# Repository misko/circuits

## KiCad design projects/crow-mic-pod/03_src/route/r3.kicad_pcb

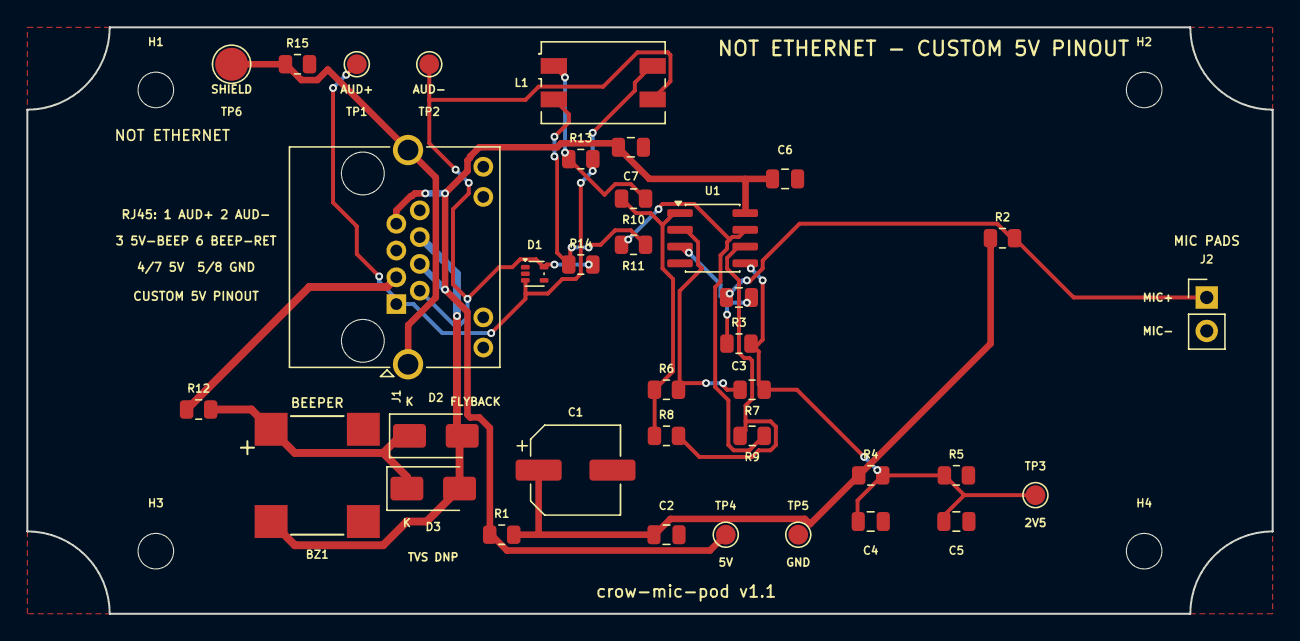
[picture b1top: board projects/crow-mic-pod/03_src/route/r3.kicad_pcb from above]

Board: 2 copper layers, 94.5 x 44.5 mm, 40 parts (0 on the bottom side), 18 nets.

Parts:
BZ1: CMT-8504-100-SMT-TR; CMT-8504
C1: 100u 5VF; CP_Elec_6.3x5.4
C2: 100n 5VF; C_0805_2012Metric
C3: 1u coupling; C_0805_2012Metric
C4: 10u VMID; C_0805_2012Metric
C5: 100n VMID; C_0805_2012Metric
C6: 100n U1; C_0805_2012Metric
C7: 10u 5V bulk; C_0805_2012Metric
D1: TPD2E2U06DRLR; SOT-553
D2: SS14 flyback; D_SMA
D3: SMAJ6.0A TVS DNP; D_SMA
H1, H2, H3, H4: MountingHole_2.7mm_M2.5
J1: RJHSE-5384; RJ45_Amphenol_RJHSE538X
J2: MIC PADS (AOM-5024L); PinHeader_1x02_P2.54mm_Vertical
L1: CM choke DNP; L_CommonMode_Wuerth_WE-SL2
R1: 100R 5VF; R_0805_2012Metric
R2: 3.9k mic bias; R_0805_2012Metric
R3: 100k bias; R_0805_2012Metric
R4: 10k div hi; R_0805_2012Metric
R5: 10k div lo; R_0805_2012Metric
R6: 10k fb A; R_0805_2012Metric
R7: 20k gain A; R_0805_2012Metric
R8: 20k inv in; R_0805_2012Metric
R9: 20k inv fb; R_0805_2012Metric
R10: 68R iso +; R_0805_2012Metric
R11: 68R iso -; R_0805_2012Metric
R12: 0R beep series; R_0805_2012Metric
R13: 0R choke byp +; R_0805_2012Metric
R14: 0R choke byp -; R_0805_2012Metric
R15: shield bond DNP; R_0805_2012Metric
TP1: TP AUDIO+; TestPoint_Pad_D1.5mm
TP2: TP AUDIO-; TestPoint_Pad_D1.5mm
TP3: TP 2V5 MID; TestPoint_Pad_D1.5mm
TP4: TP 5V; TestPoint_Pad_D1.5mm
TP5: TP GND; TestPoint_Pad_D1.5mm
TP6: SHIELD BOND PAD; TestPoint_Pad_D2.5mm
U1: OPA1678IDR; SOIC-8_3.9x4.9mm_P1.27mm

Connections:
5V: C6.1, C7.1, J1.4, J1.7, R1.1, TP4.1, U1.8
5VF: C1.1, C2.1, R1.2, R2.1, R4.1
AIN: C3.2, R3.1, U1.3
AUDIO_N: D1.5, J1.2, L1.3, R14.2, TP2.1
AUDIO_P: D1.3, J1.1, L1.4, R13.2, TP1.1
AUD_N_I: L1.2, R11.2, R14.1
AUD_P_I: L1.1, R10.2, R13.1
A_OUT: R6.1, R8.1, R10.1, U1.1
BEEP_5V: J1.3, R12.1
BEEP_RET: BZ1.2, D2.2, D3.2, J1.6
BZ_P: BZ1.1, D2.1, D3.1, R12.2
B_OUT: R9.2, R11.1, U1.7
FB_A: R6.2, R7.1, U1.2
FB_B: R8.2, R9.1, U1.6
GND: C1.2, C2.2, C4.2, C5.2, C6.2, C7.2, D1.4, J1.5, J1.8, J2.2, R5.2, R15.2, TP5.1, U1.4
MIC: C3.1, J2.1, R2.2
SHIELD: J1.SH, R15.1, TP6.1
VMID: C4.1, C5.1, R3.2, R4.2, R5.1, R7.2, TP3.1, U1.5

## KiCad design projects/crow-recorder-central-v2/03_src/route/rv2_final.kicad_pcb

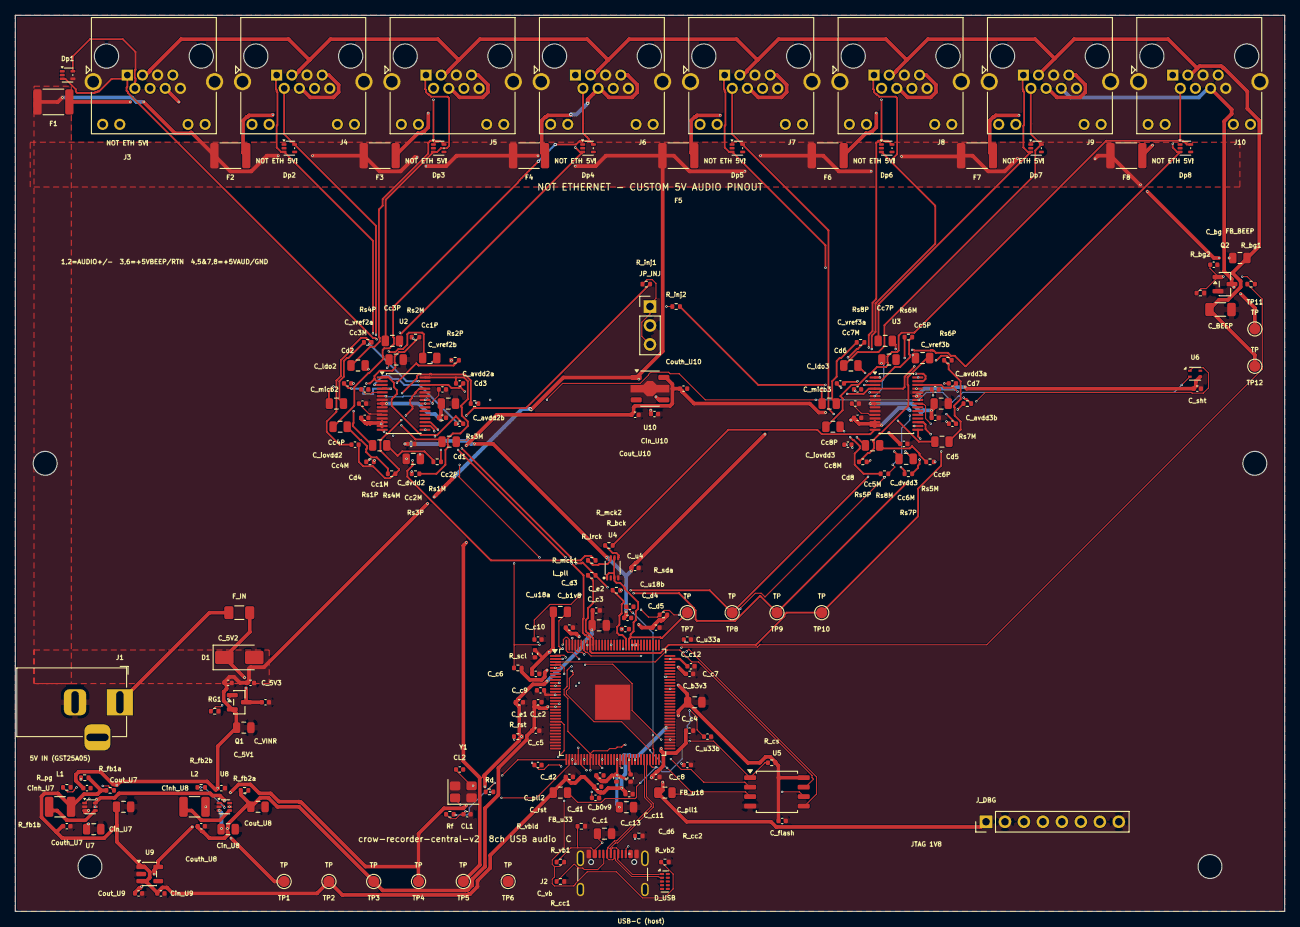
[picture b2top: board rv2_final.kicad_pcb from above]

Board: 6 copper layers, 170.0 x 120.0 mm, 203 parts (0 on the bottom side), 116 nets.

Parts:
CL1, CL2: 12pF; C_0402_1005Metric
C_5V1: 22uF; C_0805_2012Metric
C_5V2, C_5V3: 100nF; C_0402_1005Metric
C_BEEP: 47uF; C_1206_3216Metric
C_VINR: 100nF; C_0402_1005Metric
C_avdd2a, C_avdd3a: 10uF; C_0805_2012Metric
C_avdd2b, C_avdd3b: 100nF; C_0402_1005Metric
C_b0v9, C_b1v8, C_b3v3: 10uF; C_0805_2012Metric
C_bg: 4.7nF; C_0402_1005Metric
C_c1, C_c2, C_c3, C_c4, C_c5, C_c6, C_c7, C_c8, C_c9, C_c10, C_c11, C_c12, C_c13: 100nF; C_0402_1005Metric
C_d1, C_d2, C_d3, C_d4, C_d5, C_d6: 100nF; C_0402_1005Metric
C_dvdd2, C_dvdd3: 100nF; C_0402_1005Metric
C_e1, C_e2: 100nF; C_0402_1005Metric
C_flash: 100nF; C_0402_1005Metric
C_iovdd2, C_iovdd3: 100nF; C_0402_1005Metric
C_ldo2, C_ldo3: 1uF; C_0402_1005Metric
C_micb2, C_micb3: 1uF; C_0402_1005Metric
C_pll1: 1uF; C_0402_1005Metric
C_pll2: 100nF; C_0402_1005Metric
C_rst: 100nF; C_0402_1005Metric
C_sht: 100nF; C_0402_1005Metric
C_u4, C_u18b, C_u33b: 100nF; C_0402_1005Metric
C_u18a, C_u33a: 1uF; C_0402_1005Metric
C_vb: 2.2uF; C_0805_2012Metric
C_vref2a, C_vref3a: 10uF; C_0805_2012Metric
C_vref2b, C_vref3b: 100nF; C_0402_1005Metric
Cc1M, Cc1P, Cc2M, Cc2P, Cc3M, Cc3P, Cc4M, Cc4P, Cc5M, Cc5P, Cc6M, Cc6P, Cc7M, Cc7P, Cc8M, Cc8P: 2.2uF; C_0805_2012Metric
Cd1, Cd2, Cd3, Cd4, Cd5, Cd6, Cd7, Cd8: 1nF; C_0402_1005Metric
Cin_U7, Cin_U8: 10uF; C_0805_2012Metric
Cin_U9, Cin_U10: 1uF; C_0402_1005Metric
Cinh_U7, Cinh_U8: 100nF; C_0402_1005Metric
Cout_U7, Cout_U8: 22uF; C_0805_2012Metric
Cout_U9: 1uF; C_0402_1005Metric
Cout_U10: 2.2uF; C_0402_1005Metric
Couth_U7, Couth_U8, Couth_U10: 100nF; C_0402_1005Metric
D1: C87074; D_SMA
D_USB: C90627; USON-10_2.5x1.0mm_P0.5mm
Dp1, Dp2, Dp3, Dp4, Dp5, Dp6, Dp7, Dp8: C1972959; SOT-553
F1, F2, F3, F4, F5, F6, F7, F8: C2649901; Fuse_1812_4532Metric
FB_BEEP: simple_inductor; C_0805_2012Metric
FB_u18, FB_u33: simple_inductor; C_0805_2012Metric
F_IN: C136345; Fuse_1206_3216Metric
H1, H2, H3, H4: MountingHole_3.2mm_M3
J1: C381116; BarrelJack_Horizontal
J2: C3020560; USB4105_GCT_16P_TopMnt_num
J3, J4, J5, J6, J7, J8, J9, J10: C9900035627; RJ45_RJHSE538X_num
JP_INJ: simple_chip; PinHeader_1x03_P2.54mm_Vertical
J_DBG: simple_chip; PinHeader_1x08_P2.54mm_Vertical
L1, L2: simple_inductor; C_1210_3225Metric
L_pll: simple_inductor; C_0805_2012Metric
Q1: C15127; SOT-23
Q2: C20917; SOT-23
RG1: 10kΩ; R_0402_1005Metric
R_bck: 33Ω; R_0402_1005Metric
R_bg1: 1kΩ; R_0402_1005Metric
R_bg2: 100kΩ; R_0402_1005Metric
R_cc1, R_cc2: 5.1kΩ; R_0402_1005Metric
R_cs: 10kΩ; R_0402_1005Metric
R_fb1a, R_fb2a: 200kΩ; R_0402_1005Metric
R_fb1b: 44.2kΩ; R_0402_1005Metric
R_fb2b: 402kΩ; R_0402_1005Metric
R_inj1, R_inj2: 1kΩ; R_0402_1005Metric
R_lrck: 33Ω; R_0402_1005Metric
R_mck1, R_mck2: 33Ω; R_0402_1005Metric
R_pg: 100kΩ; R_0402_1005Metric
R_rst: 10kΩ; R_0402_1005Metric
R_scl: 4.7kΩ; R_0402_1005Metric
R_sda: 4.7kΩ; R_0402_1005Metric
R_vb1: 220kΩ; R_0402_1005Metric
R_vb2: 330kΩ; R_0402_1005Metric
R_vbld: 47kΩ; R_0402_1005Metric
Rd: 680Ω; R_0402_1005Metric
Rf: 1MΩ; R_0402_1005Metric
Rs1M, Rs1P, Rs2M, Rs2P, Rs3M, Rs3P, Rs4M, Rs4P, Rs5M, Rs5P, Rs6M, Rs6P, Rs7M, Rs7P, Rs8M, Rs8P: 100Ω; R_0402_1005Metric
TP1, TP2, TP3, TP4, TP5, TP6, TP7, TP8, TP9, TP10, TP11, TP12: TP; TestPoint_Pad_D1.5mm
U1: C6938291; TQFP-128_14x14mm_P0.4mm_EP_XU316
U2, U3: C181312; TSSOP-30_4.4x7.8mm_P0.5mm
U4: C232798; US8_MO-187CA_P0.5mm_NC7NZ34
U5: C82317; SOIC-8_5.3x5.3mm_P1.27mm
U6: C2909890; Sensirion_DFN-4_1.5x1.5mm_P0.8mm_SHT4x_NoCentralPad
U7, U8: C5224055; SOT-563
U9: C79924; SOT-23-5
U10: C6035451; SOT-89-5
Y1: C2762192; Crystal_SMD_SeikoEpson_FA238-4Pin_3.2x2.5mm

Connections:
0V9: C_b0v9.1, C_c1.1, C_c2.1, C_c3.1, C_c4.1, C_c5.1, C_c6.1, C_c7.1, C_c8.1, C_c9.1, C_c10.1, C_c11.1, C_c12.1, C_c13.1, Cout_U8.1, Couth_U8.1, L2.2, L_pll.1, R_fb2a.1, TP3.1, U1.5, U1.11, U1.14, U1.18, U1.39, U1.45, U1.50, U1.54, U1.68, U1.85, U1.95, U1.104, U1.105, U1.106, U1.113
1V8: C_b1v8.1, C_e1.1, C_e2.1, Cout_U9.1, FB_u18.1, J_DBG.1, R_rst.2, TP4.1, U1.35, U1.56, U9.5
3V3: C_b3v3.1, C_d1.1, C_d2.1, C_d3.1, C_d4.1, C_d5.1, C_d6.1, C_dvdd2.1, C_dvdd3.1, C_flash.1, C_iovdd2.1, C_iovdd3.1, C_sht.1, C_u4.1, Cin_U9.1, Cout_U7.1, Couth_U7.1, FB_u33.1, L1.2, R_cs.2, R_fb1a.1, R_pg.2, R_scl.2, R_sda.2, TP2.1, U1.10, U1.17, U1.72, U1.89, U1.109, U1.121, U2.13, U2.14, U3.13, U3.14, U3.25, U4.8, U5.8, U6.3, U9.1, U9.3
3V3A: C_avdd2a.1, C_avdd2b.1, C_avdd3a.1, C_avdd3b.1, Cout_U10.1, Couth_U10.1, TP5.1, U2.8, U3.8, U10.5
5V: C_5V1.1, C_5V2.1, C_5V3.1, Cin_U7.1, Cin_U8.1, Cin_U10.1, Cinh_U7.1, Cinh_U8.1, F1.1, F2.1, F3.1, F4.1, F5.1, F6.1, F7.1, F8.1, FB_BEEP.1, Q1.2, TP1.1, U7.3, U7.5, U8.3, U10.1, U10.4
ADC1M: Cd1.2, Rs1M.2, U2.1
ADC1P: Cd1.1, R_inj1.2, Rs1P.2, U2.3
ADC2M: Cd2.2, Rs2M.2, U2.2
ADC2P: Cd2.1, Rs2P.2, U2.4
ADC3M: Cd3.2, Rs3M.2, U2.28
ADC3P: Cd3.1, Rs3P.2, U2.30
ADC4M: Cd4.2, Rs4M.2, U2.27
ADC4P: Cd4.1, Rs4P.2, U2.29
ADC5M: Cd5.2, Rs5M.2, U3.1
ADC5P: Cd5.1, R_inj2.2, Rs5P.2, U3.3
ADC6M: Cd6.2, Rs6M.2, U3.2
ADC6P: Cd6.1, Rs6P.2, U3.4
ADC7M: Cd7.2, Rs7M.2, U3.28
ADC7P: Cd7.1, Rs7P.2, U3.30
ADC8M: Cd8.2, Rs8M.2, U3.27
ADC8P: Cd8.1, Rs8P.2, U3.29
ADC_DIN: TP10.1, U1.120, U2.18, U3.18
AUDIO1M: Cc1M.1, Dp1.5, J3.2
AUDIO1P: Cc1P.1, Dp1.3, J3.1
AUDIO2M: Cc2M.1, Dp2.5, J4.2
AUDIO2P: Cc2P.1, Dp2.3, J4.1
AUDIO3M: Cc3M.1, Dp3.5, J5.2
AUDIO3P: Cc3P.1, Dp3.3, J5.1
AUDIO4M: Cc4M.1, Dp4.5, J6.2
AUDIO4P: Cc4P.1, Dp4.3, J6.1
AUDIO5M: Cc5M.1, Dp5.5, J7.2
AUDIO5P: Cc5P.1, Dp5.3, J7.1
AUDIO6M: Cc6M.1, Dp6.5, J8.2
AUDIO6P: Cc6P.1, Dp6.3, J8.1
AUDIO7M: Cc7M.1, Dp7.5, J9.2
AUDIO7P: Cc7P.1, Dp7.3, J9.1
AUDIO8M: Cc8M.1, Dp8.5, J10.2
AUDIO8P: Cc8P.1, Dp8.3, J10.1
BCLK: R_bck.2, TP8.1, U2.17, U3.17
BCLK_SRC: R_bck.1, U1.108
BEEP_G: C_bg.1, Q2.1, R_bg1.2, R_bg2.1
BEEP_GATE: R_bg1.1, U1.122
BEEP_RETURN: J3.6, J4.6, J5.6, J6.6, J7.6, J8.6, J9.6, J10.6, Q2.3, TP11.1
CC1: J2.3, R_cc1.1
CC2: J2.11, R_cc2.1
FB1: R_fb1a.2, R_fb1b.1, U7.1
FB2: R_fb2a.2, R_fb2b.1, U8.1
GATE_RPP: Q1.1, RG1.1
GND: CL1.2, CL2.2, C_5V1.2, C_5V2.2, C_5V3.2, C_BEEP.2, C_VINR.2, C_avdd2a.2, C_avdd2b.2, C_avdd3a.2, C_avdd3b.2, C_b0v9.2, C_b1v8.2, C_b3v3.2, C_bg.2, C_c1.2, C_c2.2, C_c3.2, C_c4.2, C_c5.2, C_c6.2, C_c7.2, C_c8.2, C_c9.2, C_c10.2, C_c11.2, C_c12.2, C_c13.2, C_d1.2, C_d2.2, C_d3.2, C_d4.2, C_d5.2, C_d6.2, C_dvdd2.2, C_dvdd3.2, C_e1.2, C_e2.2, C_flash.2, C_iovdd2.2, C_iovdd3.2, C_ldo2.2, C_ldo3.2, C_micb2.2, C_micb3.2, C_pll1.2, C_pll2.2, C_rst.2, C_sht.2, C_u4.2, C_u18a.2, C_u18b.2, C_u33a.2, C_u33b.2, C_vb.2, C_vref2a.2, C_vref2b.2, C_vref3a.2, C_vref3b.2, Cin_U7.2, Cin_U8.2, Cin_U9.2, Cin_U10.2, Cinh_U7.2, Cinh_U8.2, Cout_U7.2, Cout_U8.2, Cout_U9.2, Cout_U10.2, Couth_U7.2, Couth_U8.2, Couth_U10.2, D1.2, D_USB.3, D_USB.8, Dp1.4, Dp2.4, Dp3.4, Dp4.4, Dp5.4, Dp6.4, Dp7.4, Dp8.4, J1.2, J2.1, J2.8, J2.9, J2.16, J2.17, J3.5, J3.8, J3.13, J4.5, J4.8, J4.13, J5.5, J5.8, J5.13, J6.5, J6.8, J6.13, J7.5, J7.8, J7.13, J8.5, J8.8, J8.13, J9.5, J9.8, J9.13, J10.5, J10.8, J10.13, JP_INJ.2, J_DBG.2, J_DBG.8, Q2.2, RG1.2, R_bg2.2, R_cc1.2, R_cc2.2, R_fb1b.2, R_fb2b.2, R_vb2.2, R_vbld.2, TP6.1, U1.24, U1.27, U1.30, U1.42, U1.129, U2.7, U2.10, U2.12, U2.25, U2.26, U3.7, U3.10, U3.12, U3.26, U4.4, U5.4, U6.4, U7.2, U8.2, U9.2, U10.2, Y1.2, Y1.4
INJ: JP_INJ.1, JP_INJ.3, R_inj1.1, R_inj2.1
JACK_IN: F_IN.1, J1.1
LDO2: C_ldo2.1, U2.11
LDO3: C_ldo3.1, U3.11
LRCK: R_lrck.2, TP9.1, U2.16, U3.16
LRCK_SRC: R_lrck.1, U1.119
MCLK: TP7.1, U1.107, U4.1, U4.3, U4.6
MCLK_A1: R_mck1.2, U2.15
MCLK_A2: R_mck2.2, U3.15
MCLK_B1: R_mck1.1, U4.7
MCLK_B2: R_mck2.1, U4.5
MICBIAS2: C_micb2.1, U2.5
MICBIAS3: C_micb3.1, U3.5
MID1M: Cc1M.2, Rs1M.1
MID1P: Cc1P.2, Rs1P.1
MID2M: Cc2M.2, Rs2M.1
MID2P: Cc2P.2, Rs2P.1
MID3M: Cc3M.2, Rs3M.1
MID3P: Cc3P.2, Rs3P.1
MID4M: Cc4M.2, Rs4M.1
MID4P: Cc4P.2, Rs4P.1
MID5M: Cc5M.2, Rs5M.1
MID5P: Cc5P.2, Rs5P.1
MID6M: Cc6M.2, Rs6M.1
MID6P: Cc6P.2, Rs6P.1
MID7M: Cc7M.2, Rs7M.1
MID7P: Cc7P.2, Rs7P.1
MID8M: Cc8M.2, Rs8M.1
MID8P: Cc8P.2, Rs8P.1
P5VA_1: F1.2, J3.4, J3.7
P5VA_2: F2.2, J4.4, J4.7
P5VA_3: F3.2, J5.4, J5.7
P5VA_4: F4.2, J6.4, J6.7
P5VA_5: F5.2, J7.4, J7.7
P5VA_6: F6.2, J8.4, J8.7
P5VA_7: F7.2, J9.4, J9.7
P5VA_8: F8.2, J10.4, J10.7
PG_3V3: R_pg.1, U7.6, U8.5
PLL_AVDD: C_pll1.1, C_pll2.1, L_pll.2, U1.41
PLUS5V_BEEP: C_BEEP.1, FB_BEEP.2, J3.3, J4.3, J5.3, J6.3, J7.3, J8.3, J9.3, J10.3, TP12.1
QSPI_CLK: U1.4, U5.6
QSPI_CS: R_cs.1, U1.2, U5.1
QSPI_D0: U1.127, U5.5
QSPI_D1: U1.128, U5.2
QSPI_D2: U1.1, U5.3
QSPI_D3: U1.3, U5.7
RST_N: C_rst.1, J_DBG.7, R_rst.1, U1.38
SCL: R_scl.1, U1.126, U2.24, U3.24, U6.2
SDA: R_sda.1, U1.125, U2.23, U3.23, U6.1
SW1: L1.1, U7.4
SW2: L2.1, U8.4
TCK: J_DBG.3, U1.51
TDI: J_DBG.5, U1.36
TDO: J_DBG.6, U1.37
TMS: J_DBG.4, U1.44
USB_DN: D_USB.2, J2.5, J2.13, U1.59
USB_DP: D_USB.1, J2.4, J2.12, U1.60
USB_VDD18: C_u18a.1, C_u18b.1, FB_u18.2, U1.62
USB_VDD33: C_u33a.1, C_u33b.1, FB_u33.2, U1.61
VBUS: C_vb.1, J2.2, J2.7, J2.10, J2.15, R_vb1.1, R_vbld.1
VBUS_SENSE: R_vb1.2, R_vb2.1, U1.23
VIN_RAW: C_VINR.1, D1.1, F_IN.2, Q1.3
VREF2: C_vref2a.1, C_vref2b.1, U2.6
VREF3: C_vref3a.1, C_vref3b.1, U3.6
XIN: CL1.1, Rf.1, U1.34, Y1.1
XOUT: Rd.1, Rf.2, U1.33
XO_XTAL: CL2.1, Rd.2, Y1.3

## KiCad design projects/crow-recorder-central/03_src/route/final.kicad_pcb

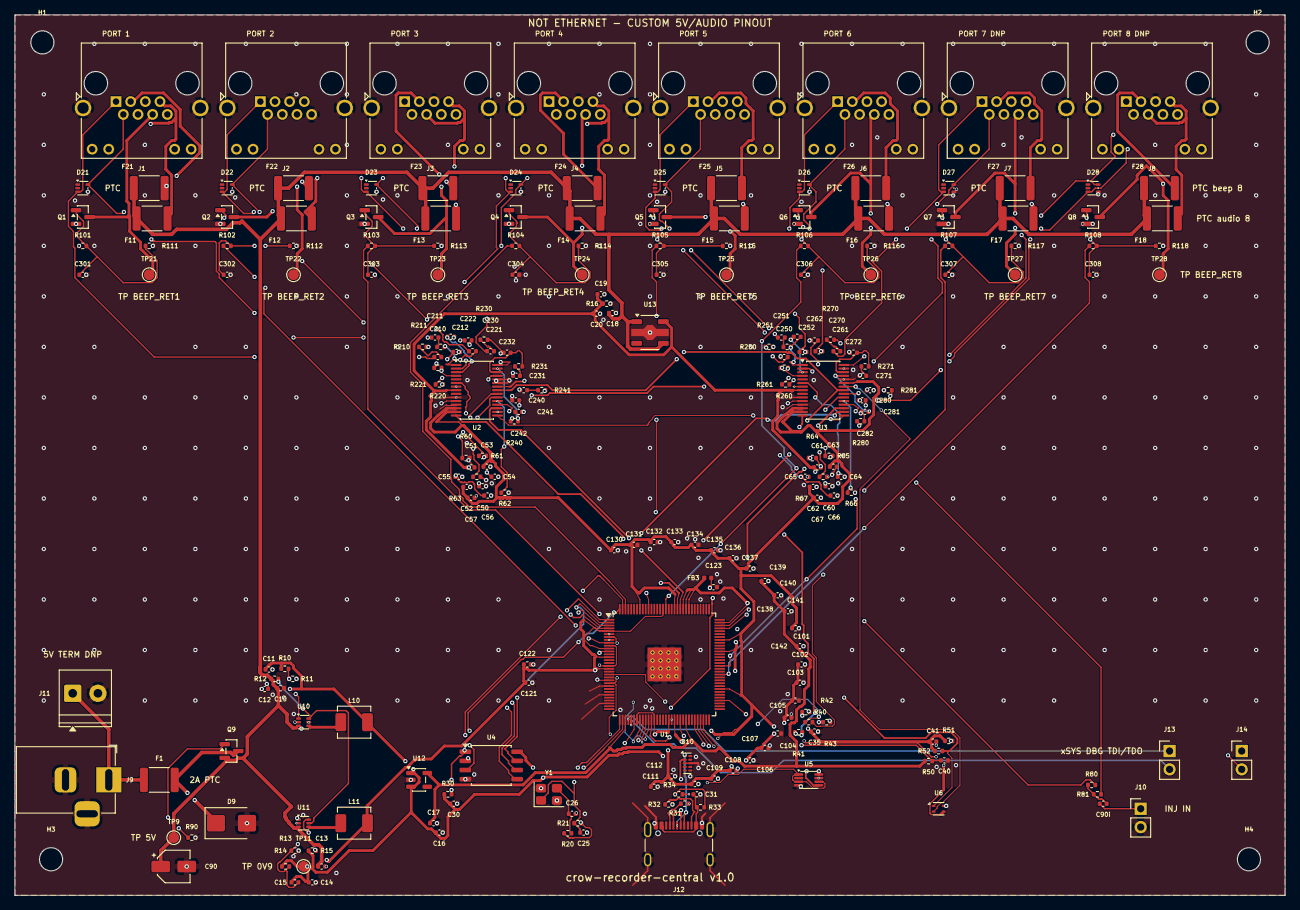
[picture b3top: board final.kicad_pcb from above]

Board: 6 copper layers, 176.0 x 122.0 mm, 238 parts (0 on the bottom side), 151 nets.

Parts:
C10, C13, C18: 4u7 VIN; C_0402_1005Metric
C11, C136, C137: 10u 3V3; C_0402_1005Metric
C12: 100p FF; C_0402_1005Metric
C14: 22u 0V9; C_0402_1005Metric
C15: 560p FF; C_0402_1005Metric
C16: 1u VIN; C_0402_1005Metric
C17: 1u 1V8; C_0402_1005Metric
C19: 10u 3V3A; C_0402_1005Metric
C20: 100n 3V3A; C_0402_1005Metric
C25: 18p CL1; C_0402_1005Metric
C26: 18p CL2; C_0402_1005Metric
C30: 100n flash; C_0402_1005Metric
C31: 1u VBUS; C_0402_1005Metric
C35: 100n buf; C_0402_1005Metric
C40: 10n RST; C_0402_1005Metric
C41: 100n SHT; C_0402_1005Metric
C50: 4u7 AVDD_A; C_0402_1005Metric
C51: 100n AVDD_A; C_0402_1005Metric
C52: 4u7 DVDD_A; C_0402_1005Metric
C53: 100n DVDD_A; C_0402_1005Metric
C54: 2u2 VREF_A; C_0402_1005Metric
C55: 2u2 LDO_A; C_0402_1005Metric
C56: 100n LDO_A; C_0402_1005Metric
C57: 100n IOV_A; C_0402_1005Metric
C60: 4u7 AVDD_B; C_0402_1005Metric
C61: 100n AVDD_B; C_0402_1005Metric
C62: 4u7 DVDD_B; C_0402_1005Metric
C63: 100n DVDD_B; C_0402_1005Metric
C64: 2u2 VREF_B; C_0402_1005Metric
C65: 2u2 LDO_B; C_0402_1005Metric
C66: 100n LDO_B; C_0402_1005Metric
C67: 100n IOV_B; C_0402_1005Metric
C90: 100u 5V bulk; CP_Elec_4x5.4
C90i: 1u inj; C_0402_1005Metric
C101, C102, C103, C104, C105, C106, C107, C108, C109, C110, C111, C112: 100n VDD; C_0402_1005Metric
C121, C122: 10u VDD; C_0402_1005Metric
C123: 1u PLL; C_0402_1005Metric
C130, C131, C132, C133, C134, C135: 100n 3V3; C_0402_1005Metric
C138, C139: 100n 1V8; C_0402_1005Metric
C140: 10u 1V8; C_0402_1005Metric
C141: 100n USB33; C_0402_1005Metric
C142: 100n USB18; C_0402_1005Metric
C210: 1u cpl P1; C_0402_1005Metric
C211: 1u cpl N1; C_0402_1005Metric
C212: 1n diff 1; C_0402_1005Metric
C220: 1u cpl P2; C_0402_1005Metric
C221: 1u cpl N2; C_0402_1005Metric
C222: 1n diff 2; C_0402_1005Metric
C230: 1u cpl P3; C_0402_1005Metric
C231: 1u cpl N3; C_0402_1005Metric
C232: 1n diff 3; C_0402_1005Metric
C240: 1u cpl P4; C_0402_1005Metric
C241: 1u cpl N4; C_0402_1005Metric
C242: 1n diff 4; C_0402_1005Metric
C250: 1u cpl P5; C_0402_1005Metric
C251: 1u cpl N5; C_0402_1005Metric
C252: 1n diff 5; C_0402_1005Metric
C260: 1u cpl P6; C_0402_1005Metric
C261: 1u cpl N6; C_0402_1005Metric
C262: 1n diff 6; C_0402_1005Metric
C270: 1u cpl P7; C_0402_1005Metric
C271: 1u cpl N7; C_0402_1005Metric
C272: 1n diff 7; C_0402_1005Metric
C280: 1u cpl P8; C_0402_1005Metric
C281: 1u cpl N8; C_0402_1005Metric
C282: 1n diff 8; C_0402_1005Metric
C301: 4n7 gate 1; C_0402_1005Metric
C302: 4n7 gate 2; C_0402_1005Metric
C303: 4n7 gate 3; C_0402_1005Metric
C304: 4n7 gate 4; C_0402_1005Metric
C305: 4n7 gate 5; C_0402_1005Metric
C306: 4n7 gate 6; C_0402_1005Metric
C307: 4n7 gate 7; C_0402_1005Metric
C308: 4n7 gate 8; C_0402_1005Metric
D9: SMBJ5.0A TVS; D_SMB
D10: TPD4EUSB30; USON-10_2.5x1.0mm_P0.5mm
D21: TPD2E2U06 p1; SOT-553
D22: TPD2E2U06 p2; SOT-553
D23: TPD2E2U06 p3; SOT-553
D24: TPD2E2U06 p4; SOT-553
D25: TPD2E2U06 p5; SOT-553
D26: TPD2E2U06 p6; SOT-553
D27: TPD2E2U06 p7; SOT-553
D28: TPD2E2U06 p8; SOT-553
F1: 2A PTC; Fuse_1812_4532Metric
F11: PTC audio 1; Fuse_1812_4532Metric
F12: PTC audio 2; Fuse_1812_4532Metric
F13: PTC audio 3; Fuse_1812_4532Metric
F14: PTC audio 4; Fuse_1812_4532Metric
F15: PTC audio 5; Fuse_1812_4532Metric
F16: PTC audio 6; Fuse_1812_4532Metric
F17: PTC audio 7; Fuse_1812_4532Metric
F18: PTC audio 8; Fuse_1812_4532Metric
F21: PTC beep 1; Fuse_1812_4532Metric
F22: PTC beep 2; Fuse_1812_4532Metric
F23: PTC beep 3; Fuse_1812_4532Metric
F24: PTC beep 4; Fuse_1812_4532Metric
F25: PTC beep 5; Fuse_1812_4532Metric
F26: PTC beep 6; Fuse_1812_4532Metric
F27: PTC beep 7; Fuse_1812_4532Metric
F28: PTC beep 8; Fuse_1812_4532Metric
FB3: 600R PLL; L_0402_1005Metric
H1, H2, H3, H4: MountingHole_3.2mm_M3
J1, J2, J3, J4, J5, J6: RJHSE-5384; RJ45_Amphenol_RJHSE538X
J7, J8: RJHSE-5384 DNP; RJ45_Amphenol_RJHSE538X
J9: DC-005 5V IN; BarrelJack_Horizontal
J10: INJ IN; PinHeader_1x02_P2.54mm_Vertical
J11: 5V TERM DNP; TerminalBlock_Phoenix_PT-1,5-2-3.5-H_1x02_P3.50mm_Horizontal
J12: USB4105-GF-A; USB_C_Receptacle_GCT_USB4105-xx-A_16P_TopMnt_Horizontal
J13: xSYS DBG TDI/TDO; PinHeader_1x02_P2.54mm_Vertical
J14: xSYS DBG TMS/TCK; PinHeader_1x02_P2.54mm_Vertical
L10: 1u0 3V3; L_Sunlord_MWSA0402S
L11: 1u0 0V9; L_Sunlord_MWSA0402S
Q1: AO3400A beep 1; SOT-23
Q2: AO3400A beep 2; SOT-23
Q3: AO3400A beep 3; SOT-23
Q4: AO3400A beep 4; SOT-23
Q5: AO3400A beep 5; SOT-23
Q6: AO3400A beep 6; SOT-23
Q7: AO3400A beep 7; SOT-23
Q8: AO3400A beep 8; SOT-23
Q9: AO3401A revFET; SOT-23
R10: 68k FB1 hi; R_0402_1005Metric
R11: 15k FB1 lo; R_0402_1005Metric
R12: 10k PG1 pu; R_0402_1005Metric
R13: 10k FB2 hi; R_0402_1005Metric
R14: 20k FB2 lo; R_0402_1005Metric
R15: 10k PG2 pu; R_0402_1005Metric
R16: 4k7 bleed; R_0402_1005Metric
R20: 680R Rd; R_0402_1005Metric
R21: 1M Rf; R_0402_1005Metric
R30: 10k CS pu; R_0402_1005Metric
R31: 5k1 CC1 Rd; R_0402_1005Metric
R32: 5k1 CC2 Rd; R_0402_1005Metric
R33: 220k VBUS; R_0402_1005Metric
R34: 330k VBUS; R_0402_1005Metric
R40: 33R MCLK_A; R_0402_1005Metric
R41: 33R MCLK_B; R_0402_1005Metric
R42: 33R BCLK; R_0402_1005Metric
R43: 33R LRCK; R_0402_1005Metric
R50: 10k RST pu; R_0402_1005Metric
R51: 4k7 SCL pu; R_0402_1005Metric
R52: 4k7 SDA pu; R_0402_1005Metric
R60: 100k GP0_A; R_0402_1005Metric
R61: 100k GP1_A; R_0402_1005Metric
R62: 100k GP2_A; R_0402_1005Metric
R63: 100k GP3_A; R_0402_1005Metric
R64: 100k GP0_B; R_0402_1005Metric
R65: 100k GP1_B; R_0402_1005Metric
R66: 100k GP2_B; R_0402_1005Metric
R67: 100k GP3_B; R_0402_1005Metric
R80: 1k inj ch4; R_0402_1005Metric
R81: 1k inj ch8; R_0402_1005Metric
R90: 100k FET gate; R_0402_1005Metric
R101: 1k gate 1; R_0402_1005Metric
R102: 1k gate 2; R_0402_1005Metric
R103: 1k gate 3; R_0402_1005Metric
R104: 1k gate 4; R_0402_1005Metric
R105: 1k gate 5; R_0402_1005Metric
R106: 1k gate 6; R_0402_1005Metric
R107: 1k gate 7; R_0402_1005Metric
R108: 1k gate 8; R_0402_1005Metric
R111: 100k pd 1; R_0402_1005Metric
R112: 100k pd 2; R_0402_1005Metric
R113: 100k pd 3; R_0402_1005Metric
R114: 100k pd 4; R_0402_1005Metric
R115: 100k pd 5; R_0402_1005Metric
R116: 100k pd 6; R_0402_1005Metric
R117: 100k pd 7; R_0402_1005Metric
R118: 100k pd 8; R_0402_1005Metric
R210: 49R9 P1; R_0402_1005Metric
R211: 49R9 N1; R_0402_1005Metric
R220: 49R9 P2; R_0402_1005Metric
R221: 49R9 N2; R_0402_1005Metric
R230: 49R9 P3; R_0402_1005Metric
R231: 49R9 N3; R_0402_1005Metric
R240: 49R9 P4; R_0402_1005Metric
R241: 49R9 N4; R_0402_1005Metric
R250: 49R9 P5; R_0402_1005Metric
R251: 49R9 N5; R_0402_1005Metric
R260: 49R9 P6; R_0402_1005Metric
R261: 49R9 N6; R_0402_1005Metric
R270: 49R9 P7; R_0402_1005Metric
R271: 49R9 N7; R_0402_1005Metric
R280: 49R9 P8; R_0402_1005Metric
R281: 49R9 N8; R_0402_1005Metric
TP9: TP 5V; TestPoint_Pad_D1.5mm
TP11: TP 0V9; TestPoint_Pad_D1.5mm
TP21: TP BEEP_RET1; TestPoint_Pad_D1.5mm
TP22: TP BEEP_RET2; TestPoint_Pad_D1.5mm
TP23: TP BEEP_RET3; TestPoint_Pad_D1.5mm
TP24: TP BEEP_RET4; TestPoint_Pad_D1.5mm
TP25: TP BEEP_RET5; TestPoint_Pad_D1.5mm
TP26: TP BEEP_RET6; TestPoint_Pad_D1.5mm
TP27: TP BEEP_RET7; TestPoint_Pad_D1.5mm
TP28: TP BEEP_RET8; TestPoint_Pad_D1.5mm
U1: XU316-1024-TQ128-I24; TQFP-128_14x14mm_P0.4mm_EP4.7mm
U2, U3: PCM1865DBTR; TSSOP-30_4.4x7.8mm_P0.5mm
U4: W25Q16JVSSIQ; SOIC-8_5.3x5.3mm_P1.27mm
U5: NC7NZ34 MCLK buf; VSSOP-8_2.3x2mm_P0.5mm
U6: SHT40-AD1B (0x44); Sensirion_DFN-4_1.5x1.5mm_P0.8mm_SHT4x_NoCentralPad
U10: AP61102 3V3; SOT-563
U11: AP61102 0V9; SOT-563
U12: TCR2LF18 1V8; SOT-23-5
U13: XC6227 3V3A; SOT-89-5
Y1: FA-238 24MHz; Crystal_SMD_3225-4Pin_3.2x2.5mm

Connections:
0V9: C14.1, C15.1, C101.1, C102.1, C103.1, C104.1, C105.1, C106.1, C107.1, C108.1, C109.1, C110.1, C111.1, C112.1, C121.1, C122.1, FB3.1, L11.2, R13.1, TP11.1, U1.5, U1.11, U1.14, U1.18, U1.39, U1.45, U1.50, U1.54, U1.68, U1.85, U1.95, U1.104, U1.105, U1.106, U1.113
1V8: C17.1, C138.1, C139.1, C140.1, C142.1, R50.1, U1.35, U1.56, U1.62, U12.5
3V3: C11.1, C12.1, C16.1, C30.1, C35.1, C41.1, C52.1, C53.1, C57.1, C62.1, C63.1, C67.1, C130.1, C131.1, C132.1, C133.1, C134.1, C135.1, C136.1, C137.1, C141.1, L10.2, R10.1, R15.1, R30.1, R51.1, R52.1, U1.10, U1.17, U1.40, U1.43, U1.52, U1.61, U1.72, U1.89, U1.109, U1.121, U2.13, U2.14, U3.13, U3.14, U3.25, U4.8, U5.8, U6.3, U12.1, U12.3
3V3A: C19.1, C20.1, C50.1, C51.1, C60.1, C61.1, R16.1, U2.8, U3.8, U13.5
5V: C10.1, C13.1, C18.1, C90.1, F11.1, F12.1, F13.1, F14.1, F15.1, F16.1, F17.1, F18.1, F21.1, F22.1, F23.1, F24.1, F25.1, F26.1, F27.1, F28.1, Q9.2, R12.1, TP9.1, U10.3, U10.5, U11.3, U13.1, U13.4
5V_AUD1: F11.2, J1.4, J1.7
5V_AUD2: F12.2, J2.4, J2.7
5V_AUD3: F13.2, J3.4, J3.7
5V_AUD4: F14.2, J4.4, J4.7
5V_AUD5: F15.2, J5.4, J5.7
5V_AUD6: F16.2, J6.4, J6.7
5V_AUD7: F17.2, J7.4, J7.7
5V_AUD8: F18.2, J8.4, J8.7
5V_IN: F1.1, J9.1, J11.1
5V_P: D9.1, F1.2, Q9.3
AIN_N1: C211.2, R211.1
AIN_N2: C221.2, R221.1
AIN_N3: C231.2, R231.1
AIN_N4: C241.2, R241.1
AIN_N5: C251.2, R251.1
AIN_N6: C261.2, R261.1
AIN_N7: C271.2, R271.1
AIN_N8: C281.2, R281.1
AIN_P1: C210.2, R210.1
AIN_P2: C220.2, R220.1
AIN_P3: C230.2, R230.1
AIN_P4: C240.2, R80.2, R240.1
AIN_P5: C250.2, R250.1
AIN_P6: C260.2, R260.1
AIN_P7: C270.2, R270.1
AIN_P8: C280.2, R81.2, R280.1
AUD_N1: C211.1, D21.5, J1.2
AUD_N2: C221.1, D22.5, J2.2
AUD_N3: C231.1, D23.5, J3.2
AUD_N4: C241.1, D24.5, J4.2
AUD_N5: C251.1, D25.5, J5.2
AUD_N6: C261.1, D26.5, J6.2
AUD_N7: C271.1, D27.5, J7.2
AUD_N8: C281.1, D28.5, J8.2
AUD_P1: C210.1, D21.3, J1.1
AUD_P2: C220.1, D22.3, J2.1
AUD_P3: C230.1, D23.3, J3.1
AUD_P4: C240.1, D24.3, J4.1
AUD_P5: C250.1, D25.3, J5.1
AUD_P6: C260.1, D26.3, J6.1
AUD_P7: C270.1, D27.3, J7.1
AUD_P8: C280.1, D28.3, J8.1
BCLK: R42.2, U2.17, U3.17
BCLK_X: R42.1, U1.22
BEEP_5V1: F21.2, J1.3
BEEP_5V2: F22.2, J2.3
BEEP_5V3: F23.2, J3.3
BEEP_5V4: F24.2, J4.3
BEEP_5V5: F25.2, J5.3
BEEP_5V6: F26.2, J6.3
BEEP_5V7: F27.2, J7.3
BEEP_5V8: F28.2, J8.3
BEEP_G1: R101.1, U1.6
BEEP_G2: R102.1, U1.9
BEEP_G3: R103.1, U1.12
BEEP_G4: R104.1, U1.126
BEEP_G5: R105.1, U1.118
BEEP_G6: R106.1, U1.112
BEEP_G7: R107.1, U1.80
BEEP_G8: R108.1, U1.77
BEEP_RET1: J1.6, Q1.3, TP21.1
BEEP_RET2: J2.6, Q2.3, TP22.1
BEEP_RET3: J3.6, Q3.3, TP23.1
BEEP_RET4: J4.6, Q4.3, TP24.1
BEEP_RET5: J5.6, Q5.3, TP25.1
BEEP_RET6: J6.6, Q6.3, TP26.1
BEEP_RET7: J7.6, Q7.3, TP27.1
BEEP_RET8: J8.6, Q8.3, TP28.1
BG_1: C301.1, Q1.1, R101.2, R111.1
BG_2: C302.1, Q2.1, R102.2, R112.1
BG_3: C303.1, Q3.1, R103.2, R113.1
BG_4: C304.1, Q4.1, R104.2, R114.1
BG_5: C305.1, Q5.1, R105.2, R115.1
BG_6: C306.1, Q6.1, R106.2, R116.1
BG_7: C307.1, Q7.1, R107.2, R117.1
BG_8: C308.1, Q8.1, R108.2, R118.1
BK1_PG: R12.2, U10.6, U11.5
BK1_SW: L10.1, U10.4
BK2_PG: R15.2, U11.6
BK2_SW: L11.1, U11.4
CC1: J12.A5, R31.1
CC2: J12.B5, R32.1
DATA1: U1.107, U2.18
DATA2: U1.108, U3.18
FB1: C12.2, R10.2, R11.1, U10.1
FB2: C15.2, R13.2, R14.1, U11.1
GATE9: Q9.1, R90.1
GND: C10.2, C11.2, C13.2, C14.2, C16.2, C17.2, C18.2, C19.2, C20.2, C25.2, C26.2, C30.2, C31.2, C35.2, C40.2, C41.2, C50.2, C51.2, C52.2, C53.2, C54.2, C55.2, C56.2, C57.2, C60.2, C61.2, C62.2, C63.2, C64.2, C65.2, C66.2, C67.2, C90.2, C101.2, C102.2, C103.2, C104.2, C105.2, C106.2, C107.2, C108.2, C109.2, C110.2, C111.2, C112.2, C121.2, C122.2, C123.2, C130.2, C131.2, C132.2, C133.2, C134.2, C135.2, C136.2, C137.2, C138.2, C139.2, C140.2, C141.2, C142.2, C301.2, C302.2, C303.2, C304.2, C305.2, C306.2, C307.2, C308.2, D9.2, D10.3, D10.8, D21.4, D22.4, D23.4, D24.4, D25.4, D26.4, D27.4, D28.4, J1.5, J1.8, J1.SH, J2.5, J2.8, J2.SH, J3.5, J3.8, J3.SH, J4.5, J4.8, J4.SH, J5.5, J5.8, J5.SH, J6.5, J6.8, J6.SH, J7.5, J7.8, J7.SH, J8.5, J8.8, J8.SH, J9.2, J9.3, J10.2, J11.2, J12.A1, J12.A12, J12.B1, J12.B12, J12.SH, Q1.2, Q2.2, Q3.2, Q4.2, Q5.2, Q6.2, Q7.2, Q8.2, R11.2, R14.2, R16.2, R31.2, R32.2, R34.2, R60.2, R61.2, R62.2, R63.2, R64.2, R65.2, R66.2, R67.2, R90.2, R111.2, R112.2, R113.2, R114.2, R115.2, R116.2, R117.2, R118.2, U1.24, U1.27, U1.30, U1.42, U1.129, U2.7, U2.10, U2.12, U2.25, U2.26, U3.7, U3.10, U3.12, U3.26, U4.4, U5.4, U6.4, U10.2, U11.2, U12.2, U13.2, Y1.2, Y1.4
GP0_A: R60.1, U2.22
GP0_B: R64.1, U3.22
GP1_A: R61.1, U2.21
GP1_B: R65.1, U3.21
GP2_A: R62.1, U2.20
GP2_B: R66.1, U3.20
GP3_A: R63.1, U2.19
GP3_B: R67.1, U3.19
I2C_SCL: R51.2, U1.93, U2.24, U3.24, U6.2
I2C_SDA: R52.2, U1.94, U2.23, U3.23, U6.1
INJ: C90i.1, J10.1
INJ_C: C90i.2, R80.1, R81.1
LDO_A: C55.1, C56.1, U2.11
LDO_B: C65.1, C66.1, U3.11
LRCK: R43.2, U2.16, U3.16
LRCK_X: R43.1, U1.20
MCLK_A: R40.2, U2.15
MCLK_A0: R40.1, U5.7
MCLK_B: R41.2, U3.15
MCLK_B0: R41.1, U5.5
MCLK_SRC: U1.7, U1.23, U5.1, U5.3, U5.6
PLL_AVDD: C123.1, FB3.2, U1.41
QSPI_CLK: U1.4, U4.6
QSPI_CS: R30.2, U1.2, U4.1
QSPI_D0: U1.127, U4.5
QSPI_D1: U1.128, U4.2
QSPI_D2: U1.1, U4.3
QSPI_D3: U1.3, U4.7
RST_N: C40.1, R50.2, U1.38
TCK: J14.2, U1.51
TDI: J13.1, U1.36
TDO: J13.2, U1.37
TMS: J14.1, U1.44
USB_DM: D10.2, J12.A7, J12.B7, U1.59
USB_DP: D10.1, J12.A6, J12.B6, U1.60
VA1M: C212.2, R211.2, U2.1
VA1P: C212.1, R210.2, U2.3
VA2M: C222.2, R221.2, U2.2
VA2P: C222.1, R220.2, U2.4
VA3M: C232.2, R231.2, U2.28
VA3P: C232.1, R230.2, U2.30
VA4M: C242.2, R241.2, U2.27
VA4P: C242.1, R240.2, U2.29
VB1M: C252.2, R251.2, U3.1
VB1P: C252.1, R250.2, U3.3
VB2M: C262.2, R261.2, U3.2
VB2P: C262.1, R260.2, U3.4
VB3M: C272.2, R271.2, U3.28
VB3P: C272.1, R270.2, U3.30
VB4M: C282.2, R281.2, U3.27
VB4P: C282.1, R280.2, U3.29
VBUS: C31.1, J12.A4, J12.A9, J12.B4, J12.B9, R33.1
VBUS_DET: R33.2, R34.1, U1.8
VREF_A: C54.1, U2.6
VREF_B: C64.1, U3.6
XIN: C25.1, R21.1, U1.34, Y1.1
XOUT: R20.1, R21.2, U1.33
XTAL2: C26.1, R20.2, Y1.3

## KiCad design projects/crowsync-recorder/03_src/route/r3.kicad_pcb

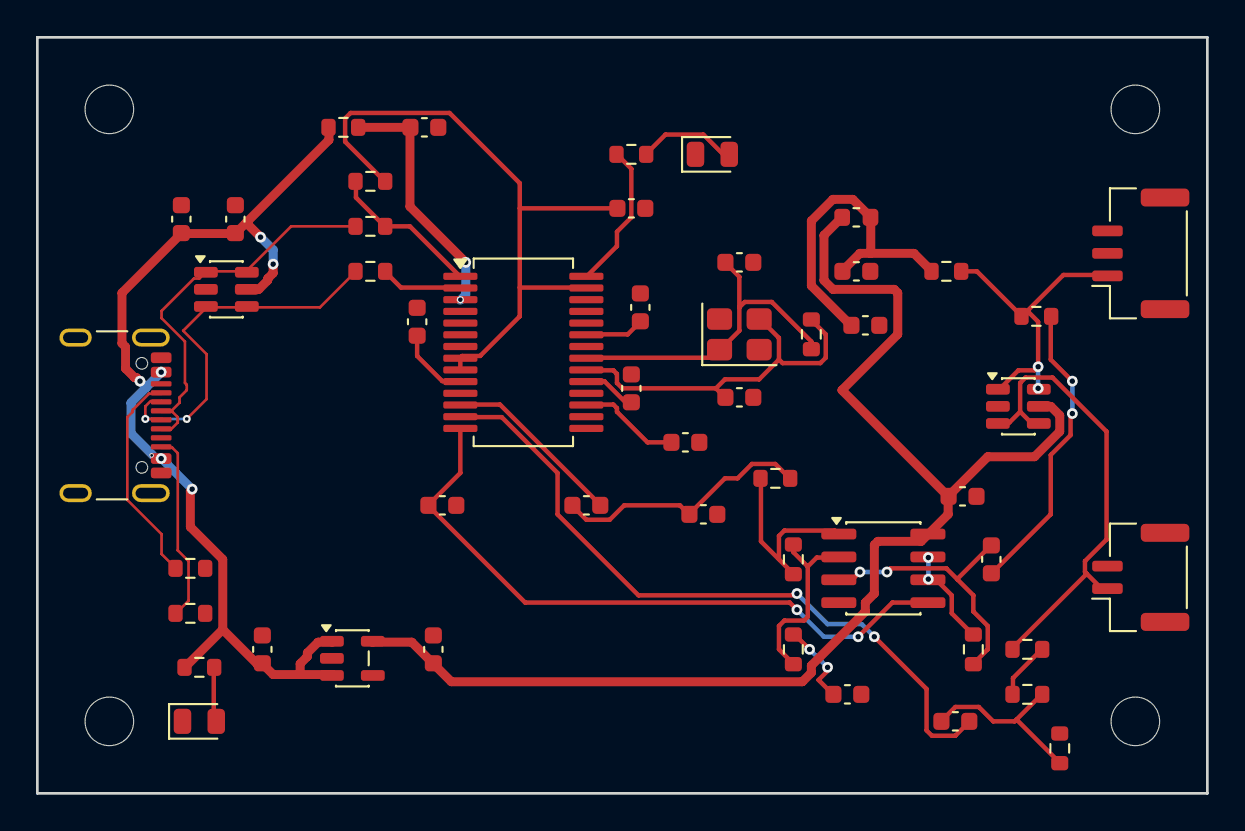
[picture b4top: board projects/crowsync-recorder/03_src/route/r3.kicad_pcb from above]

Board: 4 copper layers, 65.0 x 42.0 mm, 55 parts (0 on the bottom side), 35 nets.

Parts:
C1: 10u VCCCI; C_0603_1608Metric
C2: 10u VCOM; C_0603_1608Metric
C3: 1u VDDI; C_0603_1608Metric
C4: 1u VCCXI; C_0603_1608Metric
C5: 33p XTI; C_0603_1608Metric
C6: 33p XTO; C_0603_1608Metric
C7: 1u VCCP2I; C_0603_1608Metric
C8: 1u VCCP1I; C_0603_1608Metric
C9: 1u VINL couple; C_0603_1608Metric
C10: 1u VINR couple; C_0603_1608Metric
C11: 1u VBUS pin; C_0603_1608Metric
C12: 10u 5V bulk; C_0603_1608Metric
C13: 100n 5V; C_0603_1608Metric
C14: 1u LDO in; C_0603_1608Metric
C15: 10u 3V3A; C_0603_1608Metric
C16: 100n 3V3A U2; C_0603_1608Metric
C17: 10u bias res; C_0603_1608Metric
C18: 100n bias; C_0603_1608Metric
C19: 1u mic couple; C_0603_1608Metric
C20: 10u Cg (15.9Hz); C_0603_1608Metric
C21: 1n RF stop; C_0603_1608Metric
D1: USBLC6-2SC6 USB; SOT-23-6
D2: USBLC6-2SC6 harness; SOT-23-6
D3: green ACT; LED_0805_2012Metric
D4: green PWR; LED_0805_2012Metric
FB1: 600R@100MHz bias; L_0603_1608Metric
H1, H2, H3, H4: MountingHole_2.7mm_M2.5
J1: USB4105-GF-A; USB_C_Receptacle_GCT_USB4105-xx-A_16P_TopMnt_Horizontal
J2: JST-GH mic; JST_GH_SM03B-GHS-TB_1x03-1MP_P1.25mm_Horizontal
J3: JST-GH PPS; JST_GH_SM02B-GHS-TB_1x02-1MP_P1.25mm_Horizontal
R1: 22R D+ series; R_0603_1608Metric
R2: 22R D- series; R_0603_1608Metric
R3: 1k5 D+ pullup (VDDI); R_0603_1608Metric
R4: 5k1 Rd CC1 (UFP); R_0603_1608Metric
R5: 5k1 Rd CC2 (UFP); R_0603_1608Metric
R6: 1M XTI-XTO; R_0603_1608Metric
R7: 2R2 VBUS filter; R_0603_1608Metric
R8: 2k2 mic bias; R_0603_1608Metric
R9: 100R mic series; R_0603_1608Metric
R10: 100k bias->VCOM; R_0603_1608Metric
R11: 3k01 Rf (gain 4.0); R_0603_1608Metric
R12: 1k Rg; R_0603_1608Metric
R13: 100R amp out; R_0603_1608Metric
R14: 100R PPS series; R_0603_1608Metric
R15: 22k div top; R_0603_1608Metric
R16: 10k div bottom; R_0603_1608Metric
R17: 1k LED SSPND; R_0603_1608Metric
R18: 2k2 LED 5V; R_0603_1608Metric
U1: PCM2900CDBR; SSOP-28_5.3x10.2mm_P0.65mm
U2: TLV9062IDR; SOIC-8_3.9x4.9mm_P1.27mm
U3: TPS7A2033PDBVR; SOT-23-5
Y1: 12MHz 3225 20pF; Crystal_SMD_3225-4Pin_3.2x2.5mm

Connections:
3V3A: C15.1, C16.1, D2.5, FB1.1, U2.8, U3.5
AMP_FB: R11.2, R12.1, U2.2
AMP_INP: C19.2, R10.1, U2.3
AMP_OUT: R11.1, R13.1, U2.1
CC1: J1.A5, R4.1
CC2: J1.B5, R5.1
DM: R2.2, U1.2
DM_C: D1.3, D1.4, J1.A7, J1.B7, R2.1
DP: R1.2, R3.1, U1.1
DP_C: D1.1, D1.6, J1.A6, J1.B6, R1.1
GND: C1.2, C2.2, C3.2, C4.2, C5.2, C6.2, C7.2, C8.2, C11.2, C12.2, C13.2, C14.2, C15.2, C16.2, C17.2, C18.2, C20.2, C21.2, D1.2, D2.2, D3.1, D4.1, J1.A1, J1.A12, J1.B1, J1.B12, J1.SH, J2.2, J2.3, J2.MP, J3.2, J3.MP, R4.2, R5.2, R16.2, U1.4, U1.11, U1.18, U1.22, U1.24, U1.26, U2.4, U3.2, Y1.2, Y1.4
LED3_A: D3.2, R17.2
LED4_A: D4.2, R18.2
MIC: D2.1, D2.6, J2.1, R8.2, R9.1
MIC_BIAS_F: C17.1, C18.1, FB1.2, R8.1
MIC_IN: C19.1, R9.2
PPS: D2.3, D2.4, J3.1, R14.1
PPS_A: R14.2, R15.1
PPS_ATT: C10.1, R15.2, R16.1
RG_X: C20.1, R12.2
SSPND: R17.1, U1.28
VBUS_5V: C12.1, C13.1, C14.1, D1.5, J1.A4, J1.A9, J1.B4, J1.B9, R7.1, R18.1, U3.1, U3.3
VBUS_PCM: C11.1, R7.2, U1.3
VCCCI: C1.1, U1.10
VCCP1: C8.1, U1.17
VCCP2: C7.1, U1.19
VCCXI: C4.1, U1.23
VCOM: C2.1, U1.14, U2.5
VCOM_BUF: R10.2, U2.6, U2.7
VDDI: C3.1, R3.2, U1.8, U1.9, U1.27
VINL: C9.2, U1.12
VINL_F: C9.1, C21.1, R13.2
VINR: C10.2, U1.13
XTI: C5.1, R6.1, U1.21, Y1.1
XTO: C6.1, R6.2, U1.20, Y1.3
